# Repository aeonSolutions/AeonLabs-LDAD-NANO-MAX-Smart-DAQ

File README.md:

[PCB-Prototyping-Catalogue](https://github.com/aeonSolutions/PCB-Prototyping-Catalogue)  >>  [Laboratory Automation](https://github.com/aeonSolutions/PCB-Prototyping-Catalogue/tree/main/Laboratory%20Automation) >>  [Smart DAQs](https://github.com/aeonSolutions/PCB-Prototyping-Catalogue/tree/main/Smart%20DAQ)  >>   [12-bit Smart DAQs](https://github.com/aeonSolutions/PCB-Prototyping-Catalogue/tree/main/Smart%20DAQ/12-bit)  >>  LDAD NANO MAX Smart DAQ

<br>

# LDAD NANO MAX Smart DAQ
This repo contains the KiCad files for the AeonLabs LDAD NANO MAX Smart DAQ and more than 20 sensors compatible with I2C protocol communication. 

*Don't forget to LIKE , SHARE and subscribe the free whatsApp group* and if you liked this PCB consider buying me a cup of coffee. Links below.

  revision 6.1 Waiting for first batch from factory to be tested.

If you already tested this PCB send me a message. Thank you

## Revisions
- revision 6.1
  - added MCU firmware download connection 

## Download options
Download this repository if you need the KiCad Files pr, download the Gerber files in the release section of this repository

## Liked it ? Get a Free PCB for yourself
Send me your Device or hardware and i will design a custom PCB for it. Free of charge. Contact-me on WhatsApp or email for more info. 

## Q&A WhatsApp Group
If you have any Questions or simply  like this kind of projects and want to stay updated with the latest research ideas and prototypes during the day and week, join the WhatsApp Group
[LDAD Lab & Prototyping](https://chat.whatsapp.com/FkNC7u83kuy2QRA5sqjBVg)

## Fully assembled PCB
Alternatively, and if you do not want to build a PCB by yourself and like to buy one, you can do it here:

The price will be around 30eur plus postage fees.
(I will also deliver the assembled PCB with all the components in place at a fair aditonal cost).

#### Be supportive of my dedication and work towards technology education and buy me a coffee. Link below.

________________________________________________________________________________________________________________
## [Go back to main catalogue page](https://github.com/aeonSolutions/PCB-Prototyping-Catalogue)
________________________________________________________________________________________________________________

## PCB Parts list
- DC2DC converter HX4002B x2 : https://s.click.aliexpress.com/e/_Ak7IPx
- Capacitor 100nF SMD 1206 : https://s.click.aliexpress.com/e/_AVdmzr
- Capacitor 2.2uF SMD 1206 : https://s.click.aliexpress.com/e/_AVdmzr
- Resistor SMD 1206 330R x3 : https://s.click.aliexpress.com/e/_A7OXrR
- ESP32 WROOM32 x1 : https://s.click.aliexpress.com/e/_AF7N6l
- LED RGB x1: https://s.click.aliexpress.com/e/_AccXHT

## Firmware Download 
one can use the PCB in the repository [AeonLabs-MCU-Burner-USB-to-UART-TTL](https://github.com/aeonSolutions/AeonLabs-MCU-Burner-USB-to-UART-TTL) to program the ESP32 WROOM32 MCU on this PCB.

______________________________________________________________________________________________________________________________

### License
2022 Creative Commons Attribution-NonCommercial-ShareAlike 4.0 International

https://creativecommons.org/licenses/by-nc-sa/4.0/

### Own a copy of this work
if you like to own a copy of this work, you can buy it as a NFT or Ethereum. contact me for more details at mtpsilva@gmail.com

=====================================================================================
### Share this PCB board files

### Be supportive of my dedication and work towards technology education and buy me a coffee

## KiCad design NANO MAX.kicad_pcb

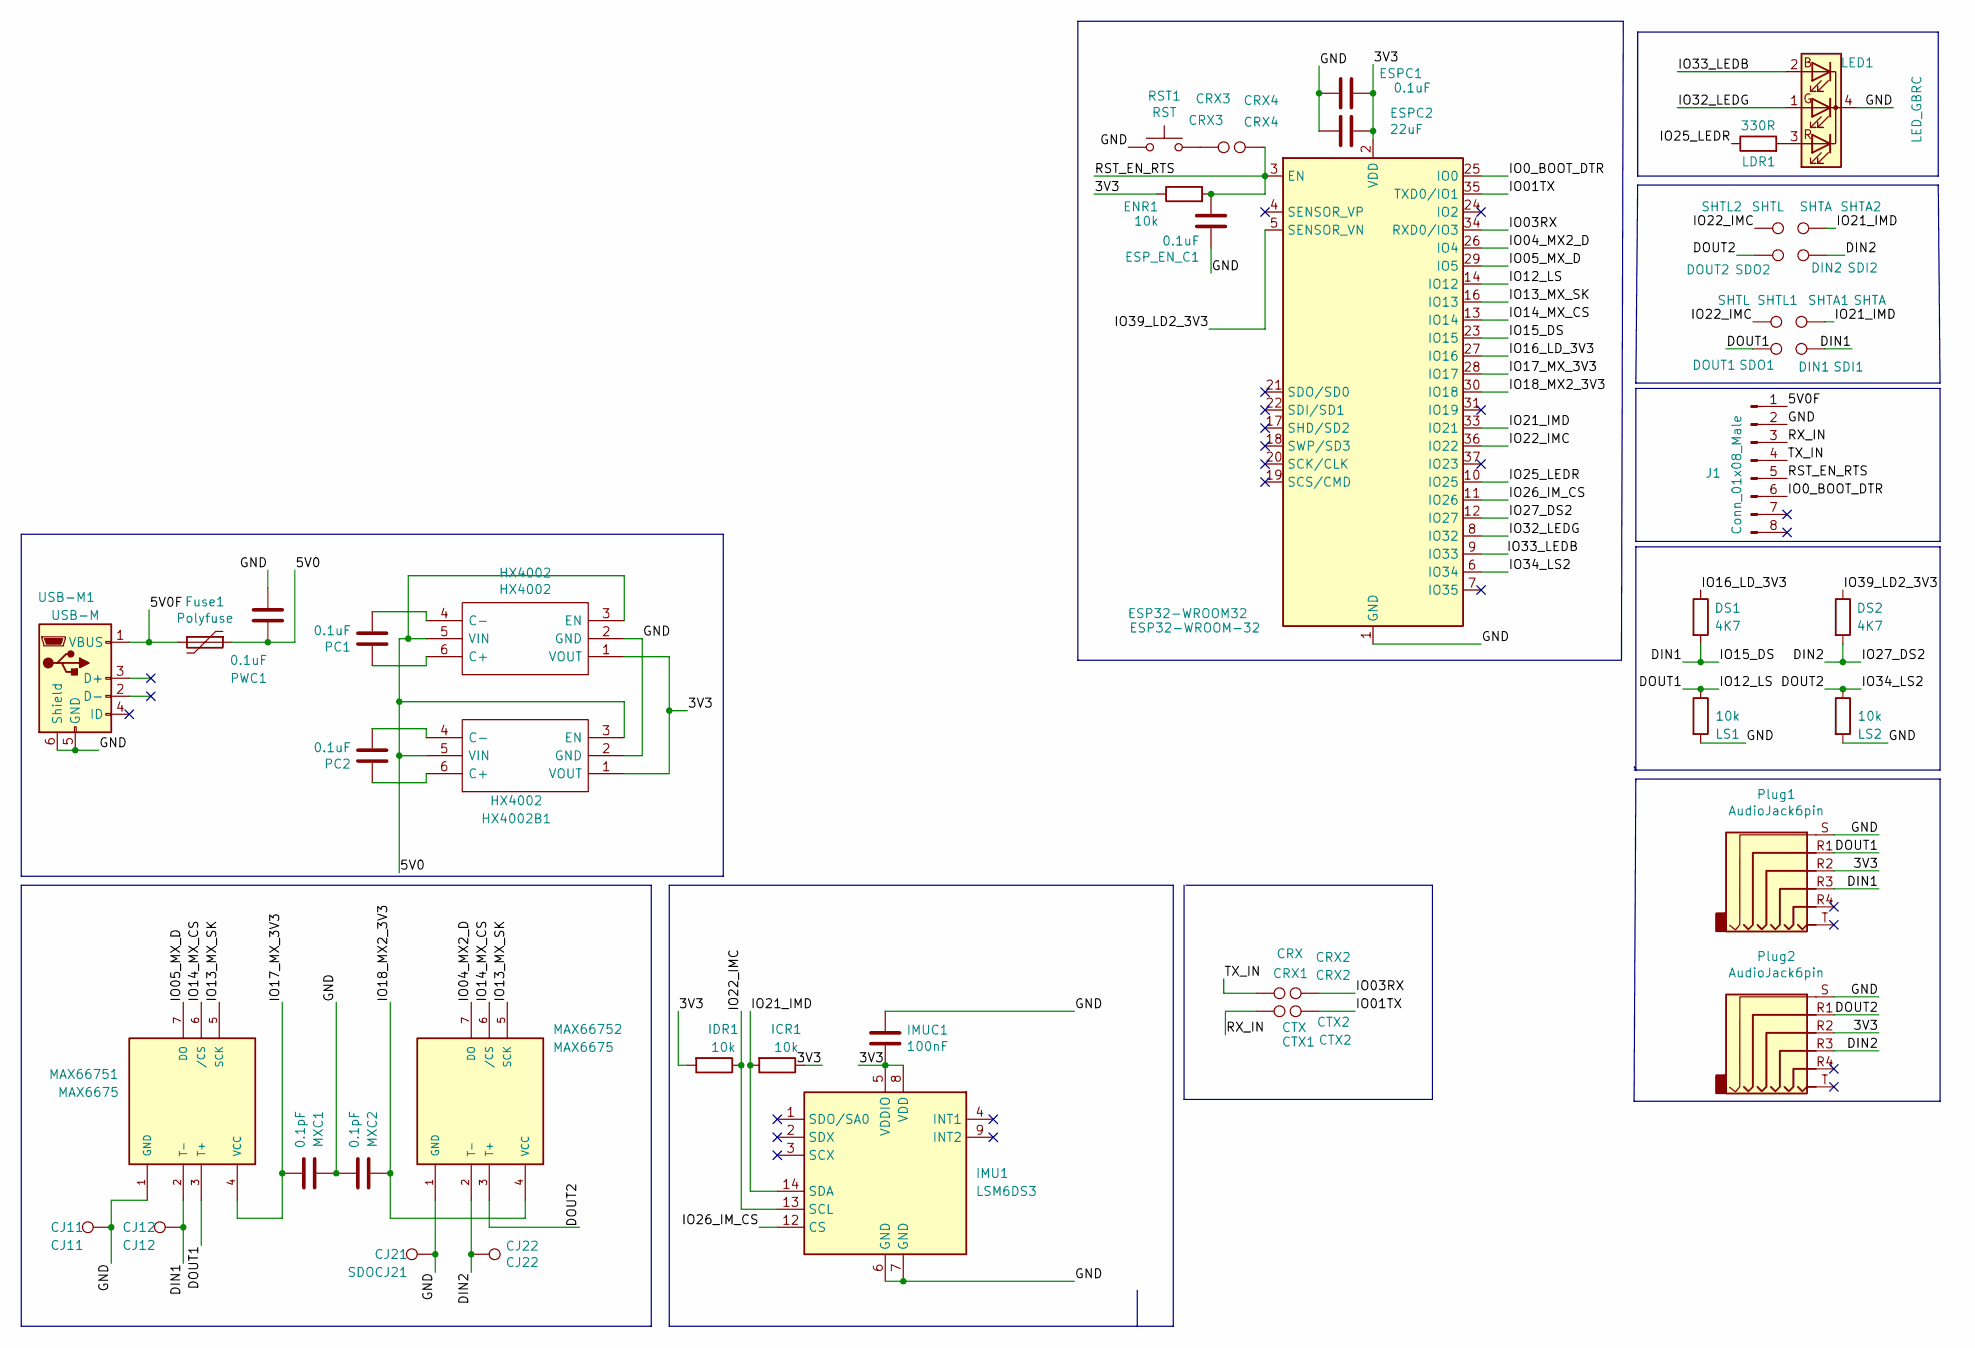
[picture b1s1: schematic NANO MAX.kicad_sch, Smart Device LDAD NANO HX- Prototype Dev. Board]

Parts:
CJ11: CJ11; TestPoint_Pad_1.0x1.0mm
CJ12: CJ12; TestPoint_Pad_1.0x1.0mm
CJ22: CJ22; TestPoint_Pad_1.0x1.0mm
CRX1: CRX; TestPoint_Pad_1.0x1.0mm
CRX2: CRX2; TestPoint_Pad_1.0x1.0mm
CRX3: CRX3; TestPoint_Pad_1.0x1.0mm
CRX4: CRX4; TestPoint_Pad_1.0x1.0mm
CTX1: CTX; TestPoint_Pad_1.0x1.0mm
CTX2: CTX2; TestPoint_Pad_1.0x1.0mm
DS1, DS2: 4K7; R_0805_2012Metric_Pad1.20x1.40mm_HandSolder
ENR1: 10k; R_0805_2012Metric_Pad1.20x1.40mm_HandSolder
ESP32-WROOM32: ESP32-WROOM-32
ESPC1: 0.1uF; C_0805_2012Metric_Pad1.18x1.45mm_HandSolder
ESPC2: 22uF; C_0805_2012Metric_Pad1.18x1.45mm_HandSolder
ESP_EN_C1: 0.1uF; C_0805_2012Metric_Pad1.18x1.45mm_HandSolder
Fuse1: Polyfuse; Fuse_1206_3216Metric
HX4002, HX4002B1: HX4002; HX4002 SOT95 P280X125-6N; Manufacturer_Part_Number HX4002
ICR1: 10k; R_True_1206_3216Metric
IDR1: 10k; R_True_1206_3216Metric
IMU1: LSM6DS3; LGA-14_3x2.5mm_P0.5mm_LayoutBorder3x4y
IMUC1: 100nF; C_0805_2012Metric_Pad1.18x1.45mm_HandSolder
J1: Conn_01x08_Male; SOIC_clipProgSmall
LDR1: 330R; R_0805_2012Metric_Pad1.20x1.40mm_HandSolder
LED1: LED_GBRC; LED_1206_3210_RGB_Metric
LS1, LS2: 10k; R_0805_2012Metric_Pad1.20x1.40mm_HandSolder
MAX66751, MAX66752: MAX6675; SOIC-8_5.275x5.275mm_P1.27mm
MXC1, MXC2: 0.1pF; C_0805_2012Metric_Pad1.18x1.45mm_HandSolder
PC1, PC2: 0.1uF; C_0805_2012Metric_Pad1.18x1.45mm_HandSolder
PWC1: 0.1uF; C_0805_2012Metric_Pad1.18x1.45mm_HandSolder
Plug1, Plug2: AudioJack6pin; Jack 2.5mm jack socket 6pin L10.5 w5.8 h3.2
RST1: RST; SW_Push_SPST_NO_Alps_SKRK AliExpress
SDI1: DIN1; TestPoint_Pad_1.0x1.0mm
SDI2: DIN2; TestPoint_Pad_1.0x1.0mm
SDO1: DOUT1; TestPoint_Pad_1.0x1.0mm
SDO2: DOUT2; TestPoint_Pad_1.0x1.0mm
SDOCJ21: CJ21; TestPoint_Pad_1.0x1.0mm
SHTA1, SHTA2: SHTA; TestPoint_Pad_1.0x1.0mm
SHTL1, SHTL2: SHTL; TestPoint_Pad_1.0x1.0mm
USB-M1: USB-M; Micro_USB_pcb_socket_5pin_4weld_points

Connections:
/3V3: ENR1.1, ESP32-WROOM32.2 (VDD), ESPC1.1, ESPC2.1, HX4002.1 (VOUT), HX4002B1.1 (VOUT), ICR1.1, IDR1.2, IMU1.5 (VDDIO), IMU1.8 (VDD), IMUC1.2, Plug1.R2, Plug2.R2
/5V0: Fuse1.1, HX4002.3 (EN), HX4002.5 (VIN), HX4002B1.3 (EN), HX4002B1.5 (VIN), PWC1.1
/5V0F: Fuse1.2, J1.1, USB-M1.1 (VBUS)
/DIN1: CJ12.1, DS1.2, ESP32-WROOM32.23 (IO15), MAX66751.2 (T-), Plug1.R3, SDI1.1
/DIN2: CJ22.1, DS2.2, ESP32-WROOM32.12 (IO27), MAX66752.2 (T-), Plug2.R3, SDI2.1
/DOUT1: ESP32-WROOM32.14 (IO12), LS1.1, MAX66751.3 (T+), Plug1.R1, SDO1.1
/DOUT2: ESP32-WROOM32.6 (IO34), LS2.1, MAX66752.3 (T+), Plug2.R1, SDO2.1
/GND: CJ11.1, ESP32-WROOM32.1 (GND), ESP32-WROOM32.15 (GND), ESP32-WROOM32.38 (GND), ESP32-WROOM32.39 (GND), ESPC1.2, ESPC2.2, ESP_EN_C1.1, HX4002.2 (GND), HX4002B1.2 (GND), IMU1.6 (GND), IMU1.7 (GND), IMUC1.1, J1.2, LED1.4 (K), LS1.2, LS2.2, MAX66751.1 (GND), MAX66752.1 (GND), MXC1.1, MXC2.2, PWC1.2, Plug1.S, Plug2.S, RST1.1, SDOCJ21.1, USB-M1.5 (GND), USB-M1.6 (Shield)
/IO0_BOOT_DTR: ESP32-WROOM32.25 (IO0), J1.6
/IO01TX: CTX2.1, ESP32-WROOM32.35 (TXD0/IO1)
/IO03RX: CRX2.1, ESP32-WROOM32.34 (RXD0/IO3)
/IO04_MX2_D: ESP32-WROOM32.26 (IO4), MAX66752.7 (DO)
/IO05_MX_D: ESP32-WROOM32.29 (IO5), MAX66751.7 (DO)
/IO13_MX_SK: ESP32-WROOM32.16 (IO13), MAX66751.5 (SCK), MAX66752.5 (SCK)
/IO14_MX_CS: ESP32-WROOM32.13 (IO14), MAX66751.6 (/CS), MAX66752.6 (/CS)
/IO16_LD_3V3: DS1.1, ESP32-WROOM32.27 (IO16)
/IO17_MX_3V3: ESP32-WROOM32.28 (IO17), MAX66751.4 (VCC), MXC1.2
/IO18_MX2_3V3: ESP32-WROOM32.30 (IO18), MAX66752.4 (VCC), MXC2.1
/IO21_IMD: ESP32-WROOM32.33 (IO21), ICR1.2, IMU1.14 (SDA), SHTA1.1, SHTA2.1
/IO22_IMC: ESP32-WROOM32.36 (IO22), IDR1.1, IMU1.13 (SCL), SHTL1.1, SHTL2.1
/IO25_LEDR: ESP32-WROOM32.10 (IO25), LDR1.1
/IO26_IM_CS: ESP32-WROOM32.11 (IO26), IMU1.12 (CS)
/IO32_LEDG: ESP32-WROOM32.8 (IO32), LED1.1 (GA)
/IO33_LEDB: ESP32-WROOM32.9 (IO33), LED1.2 (BA)
/IO39_LD2_3V3: DS2.1, ESP32-WROOM32.5 (SENSOR_VN)
/RST_EN_RTS: CRX4.1, ENR1.2, ESP32-WROOM32.3 (EN), ESP_EN_C1.2, J1.5
/RX_IN: CTX1.1, J1.3
/TX_IN: CRX1.1, J1.4
unnamed: CRX3.1, RST1.2
unnamed: HX4002.4 (C-), PC1.2
unnamed: HX4002.6 (C+), PC1.1
unnamed: HX4002B1.4 (C-), PC2.2
unnamed: HX4002B1.6 (C+), PC2.1
unnamed: LDR1.2, LED1.3 (RA)

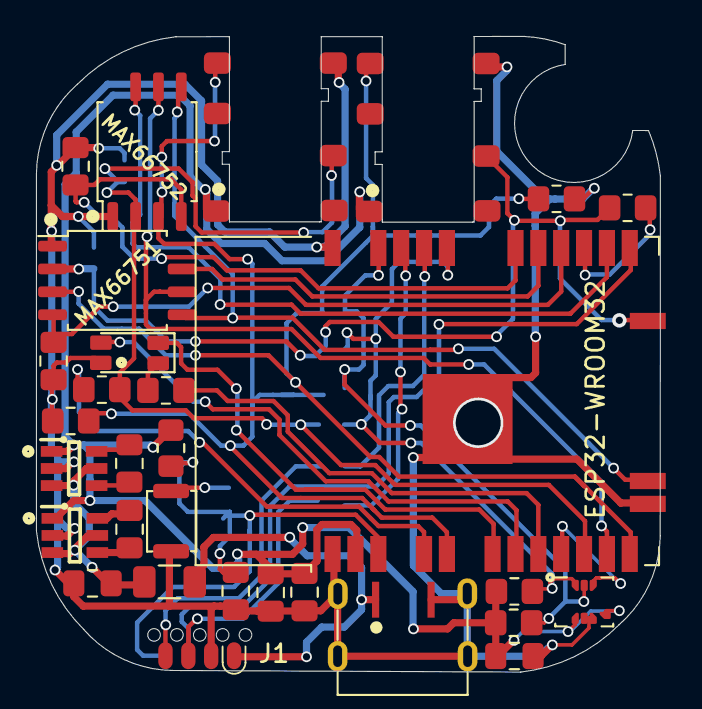
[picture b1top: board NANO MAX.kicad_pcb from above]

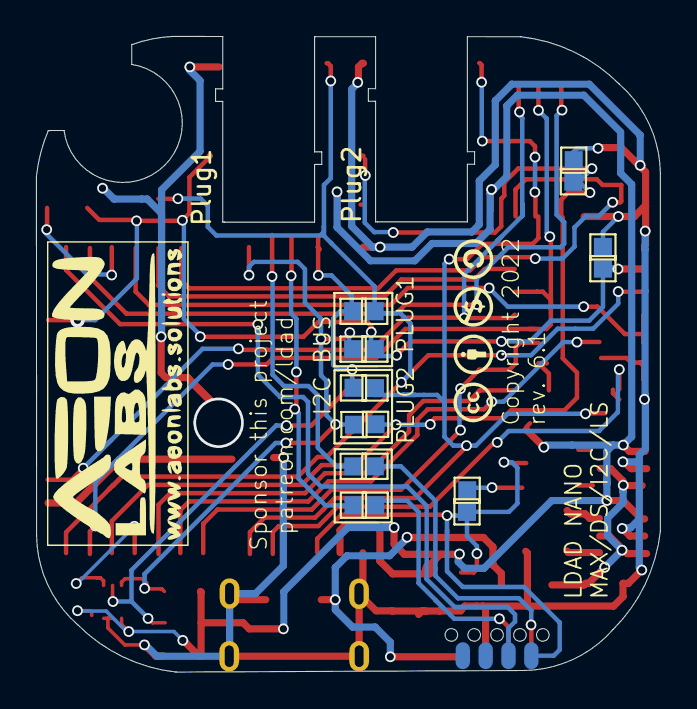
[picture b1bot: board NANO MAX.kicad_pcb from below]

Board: 2 copper layers, 34.7 x 35.3 mm, 48 parts (18 on the bottom side), 34 nets.

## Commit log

2022-04-02 init comm

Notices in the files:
NANO MAX.kicad_pcb:
Copyright 2022
